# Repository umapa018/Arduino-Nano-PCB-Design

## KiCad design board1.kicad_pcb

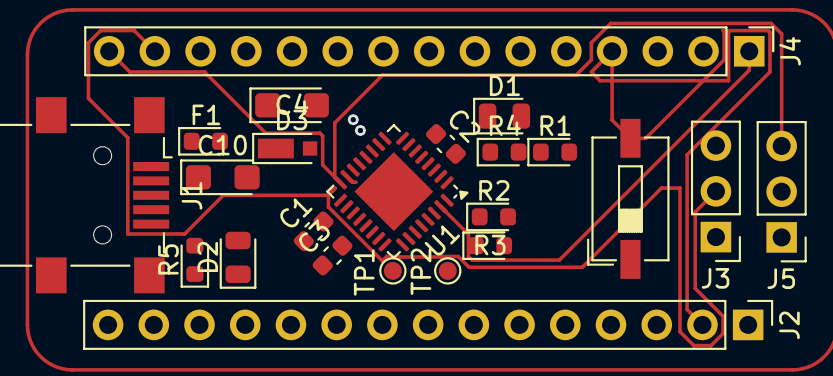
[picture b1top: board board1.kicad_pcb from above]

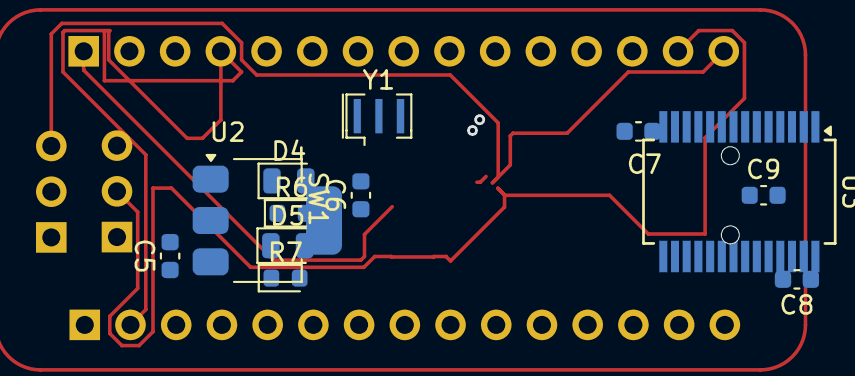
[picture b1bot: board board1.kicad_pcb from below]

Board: 4 copper layers, 35 parts (12 on the bottom side), 43 nets.

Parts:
C1, C2, C5, C6: 1u; C_0603_1608Metric
C3, C7, C8, C9: 100n; C_0603_1608Metric
C4, C10: 4u7_16v; CP_EIA-3216-10_Kemet-I
D1: YELLOW; LED_0805_2012Metric
D2, D5: GREEN; LED_0805_2012Metric
D3: diode; D_MicroSMP_AK
D4: RED; LED_0805_2012Metric
F1: 0603; D_0603_1608Metric
J1: USB_B_Mini; USB_Mini-B_Lumberg_2486_01_Horizontal
J2, J4: PinHeader_1x15_P2.54mm_Vertical
J3: ICSP; PinHeader_1x03_P2.54mm_Vertical
J5: PinHeader_1x03_P2.54mm_Vertical
R1, R5: 1k; D_0603_1608Metric
R2, R3, R4, R6, R7: 1K; D_0603_1608Metric
SW1: SW_DIP_SPSTx01_Slide_6.7x4.1mm_W6.73mm_P2.54mm_LowProfile_J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
TP1, TP2: TestPoint_Pad_D1.0mm
U1: ATmega328P-M; QFN-32-1EP_5x5mm_P0.5mm_EP3.1x3.1mm
U2: LM1117MP-5.0; SOT-223-3_TabPin2
U3: FT232RL; SSOP-28_5.3x10.2mm_P0.65mm
Y1: 16MHz; Resonator_SMD_Murata_CSTxExxV-3Pin_3.0x1.1mm

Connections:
+3V3: C7.1, J2.14, U3.17 (3V3OUT)
+5V: C1.1, C2.1, C4.1, C6.1, D3.1 (K), D4.2 (A), D5.2 (A), J2.4, J3.1, R1.1, R5.1, U1.4 (VCC), U1.6 (VCC), U1.18 (AVCC), U2.2 (VO), U3.4 (VCCIO), U3.20 (VCC)
/A0: J2.12, U1.23 (PC0)
/A1: J2.11, U1.24 (PC1)
/A2: J2.10, U1.25 (PC2)
/A3: J2.9, U1.26 (PC3)
/A4: J2.8, U1.27 (PC4)
/A5: J2.7, U1.28 (PC5)
/A6: J2.6, U1.19 (ADC6)
/A7: J2.5, U1.22 (ADC7)
/AREF: C3.1, J2.13, U1.20 (AREF)
/D0/RX: J4.2, R2.2, U1.30 (PD0)
/D1/TX: J4.1, R3.1, U1.31 (PD1)
/D2: J4.5, U1.32 (PD2)
/D3: J4.6, U1.1 (PD3)
/D4: J4.7, U1.2 (PD4)
/D5: J4.8, U1.9 (PD5)
/D6: J4.9, U1.10 (PD6)
/D7: J4.10, U1.11 (PD7)
/D8: J4.11, U1.12 (PB0)
/D9: J4.12, U1.13 (PB1)
/D10: J4.13, U1.14 (PB2)
/D11/MOSI: J3.2, J4.14, U1.15 (PB3)
/D12/MISO: J4.15, J5.3, U1.16 (PB4)
/D13/SCK: J2.15, J5.2, R4.1, U1.17 (PB5)
/D_N: J1.2 (D-), TP2.1, U3.16 (USBD-)
/D_P: J1.3 (D+), TP1.1, U3.15 (USBD+)
/RESET: C8.1, C8.2, J2.3, J4.3, J5.1, R1.2, SW1.1, U1.29 (~RESET/PC6), U3.3 (RTS)
/RX: R2.1, U3.1 (TXD)
/TX: R3.2, U3.5 (RXD)
/XTAL1: U1.7 (XTAL1/PB6), Y1.3
/XTAL2: U1.8 (XTAL2/PB7), Y1.1
GND: C1.2, C2.2, C3.2, C4.2, C5.2, C6.2, C7.2, C9.2, C10.2, D1.1 (K), D2.1 (K), J1.5 (GND), J1.6 (Shield), J2.2, J3.3, J4.4, SW1.2, U2.1 (GND), U3.7 (GND), U3.18 (GND), U3.21 (GND), U3.25 (AGND), U3.26 (TEST), Y1.2
unnamed: D1.2 (A), R4.2
unnamed: D2.2 (A), R5.2
unnamed: D4.1 (K), R6.1
unnamed: D5.1 (K), R7.1
unnamed: F1.2, J1.1 (VBUS)
unnamed: U1.3 (GND), U1.5 (GND), U1.21 (GND), U1.33 (GND)
unnamed: R6.2, U3.23 (CBUS0)
unnamed: R7.2, U3.22 (CBUS1)
VBUS: C9.1, C10.1, D3.2 (A), F1.1
VCC: C5.1, J2.1, U2.3 (VI)
